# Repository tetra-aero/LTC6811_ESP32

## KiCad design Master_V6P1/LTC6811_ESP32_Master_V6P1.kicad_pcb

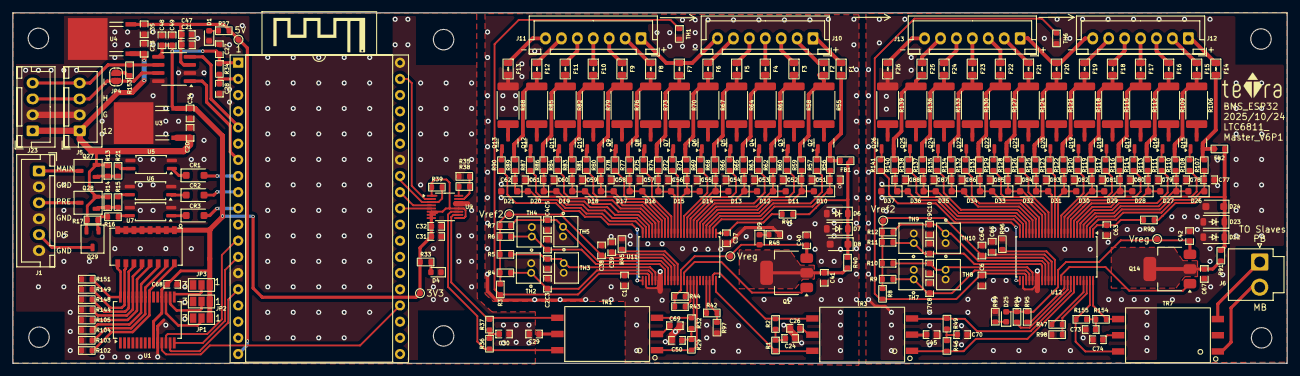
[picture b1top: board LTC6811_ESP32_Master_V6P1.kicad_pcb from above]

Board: 2 copper layers, 200.0 x 55.0 mm, 341 parts (1 on the bottom side), 253 nets.

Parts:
C1, C2, C3, C4, C5, C6, C7, C8, C9, C10, C27, C28, C32, C37, C41, C47, C49, C51, C52, C53, C54, C55, C56, C57, C58, C59, C60, C61, C62, C63, C67, C68, C77, C78, C79, C80, C81, C82, C83, C84, C85, C86, C87, C88: 100nF/100V; C_0603_1608Metric
C20, C33: 2.2uF/25V; C_0603_1608Metric
C21, C48: 1nF/16V; C_0603_1608Metric
C24, C26, C29, C30, C45, C50, C69, C70, C73, C74: 10nF/100V; C_0603_1608Metric
C31, C34, C35, C38, C39, C64, C65: 1uF/25V; C_0603_1608Metric
C40, C42: 4.7uF/16V; C_0603_1608Metric
CR1, CR2, CR3: S-562T; D_SOD-123F
D1, D4, D9, D25: LED Red; LED_0603_1608Metric
D6, D7, D22, D23: 1N4148W; D_SOD-123
D8, D24: BZT52H-C62; D_SOD-123F
D10, D11, D12, D13, D14, D15, D16, D17, D18, D19, D20, D21, D26, D27, D28, D29, D30, D31, D32, D33, D34, D35, D36, D37: PDZ7.5B; D_SOD-323_HandSoldering
F1, F2, F3, F4, F5, F6, F7, F8, F9, F10, F11, F12, F13, F14, F15, F16, F17, F18, F19, F20, F21, F22, F23, F24, F25, F26: MPZ2012S102ATD25; Fuse_0805_2012Metric
FB1, FB2: BLM18PG330SN1D; R_0603_1608Metric
J1: B6P-XH; JST_XH_B6B-XH-A_1x06_P2.50mm_Vertical
J3, J4, J7, J18, J19, J21: Hole /NC; MountingHole_3.2mm_M3_ISO7380
J5, J23: CAN; JST_XH_B4B-XH-A_1x04_P2.50mm_Vertical
J6: B2P-VH-B; JST_VH_B2P-VH-B_1x02_P3.96mm_Vertical
J10, J11, J12, J13: B7B-XH-A; JST_XH_B7B-XH-A_1x07_P2.50mm_Vertical_BAT_6S
JP1, JP2, JP3: SolderJumper_3_Bridged12; SolderJumper-3_P1.3mm_Open_Pad1.0x1.5mm_NumberLabels
JP4: SolderJumper_2_Open; SolderJumper-2_P1.3mm_Open_RoundedPad1.0x1.5mm
LOGO1, LOGO2: teTra /NC; teTra-LOGO
Q1, Q14: NSV1C201MZ4; SOT-223
Q2, Q3, Q4, Q5, Q6, Q7, Q8, Q9, Q10, Q11, Q12, Q13, Q15, Q16, Q17, Q18, Q19, Q20, Q21, Q22, Q23, Q24, Q25, Q26: TSM2323; SOT-23
Q27, Q28, Q29: SSM3J332R,LF; TSOT-23
R1, R2, R36, R37, R46, R49: 49.9R; R_0603_1608Metric
R3, R4, R5, R6, R7, R8, R9, R10, R11, R12, R13, R14, R16, R34, R102, R103, R104, R105, R144, R148, R149, R151: 10K; R_0603_1608Metric
R15, R17, R21, R35, R38, R42, R47, R97, R98: 1K; R_0603_1608Metric
R27, R33: 470R; R_0603_1608Metric
R29, R32, R154, R155: 51R; R_0603_1608Metric
R39: 2K; R_0603_1608Metric
R40, R41, R56, R59, R62, R65, R68, R71, R74, R77, R80, R83, R86, R89, R91, R92, R107, R110, R113, R116, R119, R122, R125, R128, R131, R134, R137, R140: 100R; R_0603_1608Metric
R43, R45, R94, R96: 0; R_0603_1608Metric
R44, R95: 1M; R_0603_1608Metric
R48, R99: 1.2K; R_0603_1608Metric
R55, R58, R61, R64, R67, R70, R73, R76, R79, R82, R85, R88, R106, R109, R112, R115, R118, R121, R124, R127, R130, R133, R136, R139: 36R 1W 2512; R_2512_6332Metric
R57, R60, R63, R66, R69, R72, R75, R78, R81, R84, R87, R90, R108, R111, R114, R117, R120, R123, R126, R129, R132, R135, R138, R141: 3.3K; R_0603_1608Metric
R153: 120R; R_0603_1608Metric
SW1: 218-8LPSTJ; SW_218-8LPSTJ_11.33×6.05_P1.27
TH1, TH6: 10K NTC SMD; R_0603_1608Metric
TH2, TH3, TH4, TH5, TH7, TH8, TH9, TH10: 10K NTC; JST_ZR_B2B-ZR_1x02_P1.50mm_Vertical
TP1: 5V; TestPoint_Pad_D1.0mm
TP2: 3V3; TestPoint_Pad_D1.0mm
TP3, TP5: Vreg; TestPoint_Pad_D1.0mm
TP4, TP6: Vref2; TestPoint_Pad_D1.0mm
TR1, TR3, TR7: HM2108NL
U1: MCP23017T-E/SS; SSOP-28_5.3x10.2mm_P0.65mm
U2: MCP2562T-E/SN; SOIC-8_3.9x4.9mm_P1.27mm
U3: BD33FC0FP-E2; TO252-3_ROM
U4: BD50FC0FP-E2; TO252-3_ROM
U5, U6, U7: TLP291; SOIC-4_4.55x2.6mm_P1.27mm
U8: ESP32-DevKitC V4; ESP32-DevKitc V4_DIP-38_27.9mm×48.2mm
U9: LTC6820; MSOP-16_3x4mm_P0.5mm
U11, U12: LTC6811HG-1; TSSOP-48_6.1x12.5mm_P0.5mm

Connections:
+3V3: C27.2, C31.2, C32.1, C34.2, C48.1, C49.1, C68.2, JP1.1 (A), JP2.1 (A), JP3.1 (A), R33.2, R34.1, R39.1, SW1.1, SW1.2, SW1.3, SW1.4, SW1.5, SW1.6, SW1.7, SW1.8, TP2.1, U1.9 (VDD), U1.18 (~RESET), U2.5 (Vio), U3.3 (Vo), U8.1 (3V3), U9.1 (EN), U9.6 (Vcc0), U9.7 (POL), U9.8 (PHA), U9.9 (VCC), U9.12 (MSTR)
+5V: C21.1, C35.2, C47.1, R27.2, TP1.1, U2.3 (VDD), U4.3 (Vo), U8.19 (5V)
+12V: C20.1, C33.1, J5.1, J23.1, Q27.2 (S), Q28.2 (S), Q29.2 (S), R13.2, R14.2, R16.2, U3.1 (Vcc), U4.1 (Vcc)
/CAN/CAN_H: J5.3, J23.3, JP4.1 (A), U2.7 (CANH)
/CAN/CAN_L: J5.4, J23.4, R153.1, U2.6 (CANL)
/CAN/RXD: U2.4 (RXD), U8.5 (IO34)
/CAN/TXD: U2.1 (TXD), U8.7 (IO32)
/MCU/Discharge_Relay: J1.5, Q29.3 (D)
/MCU/Discharge_Relay_Control: CR3.2, U8.10 (IO26)
/MCU/HSPI_CS: U1.11 (~CS), U8.23 (IO15)
/MCU/HSPI_MISO: U1.14 (SO), U8.13 (IO12)
/MCU/HSPI_MOSI: U1.13 (SI), U8.15 (IO13)
/MCU/HSPI_SCK: U1.12 (SCK), U8.12 (IO14)
/MCU/IM: R37.1, TR1.4, U9.10 (IM)
/MCU/IP: R36.2, TR1.6, U9.11 (IP)
/MCU/Main_Relay: J1.1, Q27.3 (D)
/MCU/Main_Relay_Control: CR1.2, U8.8 (IO33)
/MCU/NRST: C28.2, R34.2, U8.2 (EN)
/MCU/Precharge_Relay: J1.3, Q28.3 (D)
/MCU/Precharge_Relay_Control: CR2.2, U8.9 (IO25)
/MCU/VSPI_CS: U8.29 (IO5), U9.5 (CSB)
/MCU/VSPI_MISO: R39.2, U8.31 (IO19), U9.3 (MISO)
/MCU/VSPI_MOSI: U8.37 (IO23), U9.2 (MOSI)
/MCU/VSPI_SCK: U8.30 (IO18), U9.4 (SCK)
/Slaves/LTC6811_1/BAT+: D6.1 (K), D7.1 (K), D8.1 (K), FB1.1, R40.1, R41.1
/Slaves/LTC6811_1/C1: F12.1, J11.1 (Pin_2)
/Slaves/LTC6811_1/C1_G: F13.1, J11.0 (Pin_1)
/Slaves/LTC6811_1/C2: F11.1, J11.2 (Pin_3)
/Slaves/LTC6811_1/C3: F10.1, J11.3 (Pin_4)
/Slaves/LTC6811_1/C4: F9.1, J11.4 (Pin_5)
/Slaves/LTC6811_1/C5: F8.1, J11.5 (Pin_6)
/Slaves/LTC6811_1/C6: F7.1, J10.0 (Pin_1), J11.6 (Pin_7)
/Slaves/LTC6811_1/C7: F6.1, J10.1 (Pin_2)
/Slaves/LTC6811_1/C8: F5.1, J10.2 (Pin_3)
/Slaves/LTC6811_1/C9: F4.1, J10.3 (Pin_4)
/Slaves/LTC6811_1/C10: F3.1, J10.4 (Pin_5)
/Slaves/LTC6811_1/C11: F2.1, J10.5 (Pin_6)
/Slaves/LTC6811_1/C12: F1.1, J10.6 (Pin_7)
/Slaves/LTC6811_1/DRIVE: Q1.1 (B), U11.38 (DRIVE)
/Slaves/LTC6811_1/IMA: R32.1, TR1.3, U11.41 (IMA)
/Slaves/LTC6811_1/IMB: R2.1, TR3.4, U11.47 (IMB)
/Slaves/LTC6811_1/IPA: R29.2, TR1.1, U11.42 (IPA)
/Slaves/LTC6811_1/IPB: R1.2, TR3.6, U11.48 (IPB)
/Slaves/LTC6811_1/T1: C1.1, R3.2, TH1.1, U11.27 (GPIO1)
/Slaves/LTC6811_1/T2: C2.1, R4.1, TH2.1, U11.28 (GPIO2)
/Slaves/LTC6811_1/T3: C3.1, R5.1, TH3.1, U11.29 (GPIO3)
/Slaves/LTC6811_1/T4: C4.1, R6.1, TH4.1, U11.32 (GPIO4)
/Slaves/LTC6811_1/T5: C5.1, R7.1, TH5.1, U11.33 (GPIO5)
/Slaves/LTC6811_1/Vref2: C38.1, R3.1, R4.2, R5.2, R6.2, R7.2, TP4.1, U11.34 (Vref2)
/Slaves/LTC6811_1/Vreg: C40.1, D9.2 (A), Q1.3 (E), R43.2, R44.2, TP3.1, U11.37 (Vreg)
/Slaves/LTC6811_1/cell1/C: C62.1, D20.2 (A), D21.1 (K), R89.1, U11.24 (C1)
/Slaves/LTC6811_1/cell1/C+: F12.2, Q13.2 (S), R85.1, R89.2
/Slaves/LTC6811_1/cell1/S: R90.1, U11.25 (S1)
/Slaves/LTC6811_1/cell2/C: C61.1, D19.2 (A), D20.1 (K), R86.1, U11.22 (C2)
/Slaves/LTC6811_1/cell2/C+: F11.2, Q12.2 (S), R82.1, R86.2
/Slaves/LTC6811_1/cell2/S: R87.1, U11.23 (S2)
/Slaves/LTC6811_1/cell3/C: C60.1, D18.2 (A), D19.1 (K), R83.1, U11.20 (C3)
/Slaves/LTC6811_1/cell3/C+: F10.2, Q11.2 (S), R79.1, R83.2
/Slaves/LTC6811_1/cell3/S: R84.1, U11.21 (S3)
/Slaves/LTC6811_1/cell4/C: C59.1, D17.2 (A), D18.1 (K), R80.1, U11.18 (C4)
/Slaves/LTC6811_1/cell4/C+: F9.2, Q10.2 (S), R76.1, R80.2
/Slaves/LTC6811_1/cell4/S: R81.1, U11.19 (S4)
/Slaves/LTC6811_1/cell5/C: C58.1, D16.2 (A), D17.1 (K), R77.1, U11.16 (C5)
/Slaves/LTC6811_1/cell5/C+: F8.2, Q9.2 (S), R73.1, R77.2
/Slaves/LTC6811_1/cell5/S: R78.1, U11.17 (S5)
/Slaves/LTC6811_1/cell6/C: C57.1, D15.2 (A), D16.1 (K), R74.1, U11.14 (C6)
/Slaves/LTC6811_1/cell6/C+: F7.2, Q8.2 (S), R70.1, R74.2
/Slaves/LTC6811_1/cell6/S: R75.1, U11.15 (S6)
/Slaves/LTC6811_1/cell7/C: C56.1, D14.2 (A), D15.1 (K), R71.1, U11.12 (C7)
/Slaves/LTC6811_1/cell7/C+: F6.2, Q7.2 (S), R67.1, R71.2
/Slaves/LTC6811_1/cell7/S: R72.1, U11.13 (S7)
/Slaves/LTC6811_1/cell8/C: C55.1, D13.2 (A), D14.1 (K), R68.1, U11.10 (C8)
/Slaves/LTC6811_1/cell8/C+: F5.2, Q6.2 (S), R64.1, R68.2
/Slaves/LTC6811_1/cell8/S: R69.1, U11.11 (S8)
/Slaves/LTC6811_1/cell9/S: R66.1, U11.9 (S9)
/Slaves/LTC6811_1/cell10/C: C53.1, D11.2 (A), D12.1 (K), R62.1, U11.6 (C10)
/Slaves/LTC6811_1/cell10/C+: F3.2, Q4.2 (S), R58.1, R62.2
/Slaves/LTC6811_1/cell10/C-: F4.2, Q5.2 (S), R61.1, R65.2
/Slaves/LTC6811_1/cell10/CM: C54.1, D12.2 (A), D13.1 (K), R65.1, U11.8 (C9)
/Slaves/LTC6811_1/cell10/S: R63.1, U11.7 (S10)
/Slaves/LTC6811_1/cell11/C: C52.1, D10.2 (A), D11.1 (K), R59.1, U11.4 (C11)
/Slaves/LTC6811_1/cell11/C+: F2.2, Q3.2 (S), R55.1, R59.2
/Slaves/LTC6811_1/cell11/S: R60.1, U11.5 (S11)
/Slaves/LTC6811_1/cell12/C: C51.1, D10.1 (K), R56.1, U11.2 (C12)
/Slaves/LTC6811_1/cell12/C+: F1.2, FB1.2, Q2.2 (S), R56.2
/Slaves/LTC6811_1/cell12/S: R57.1, U11.3 (S12)
/Slaves/LTC6811_2/BAT+: D22.1 (K), D23.1 (K), D24.1 (K), FB2.1, R91.1, R92.1
/Slaves/LTC6811_2/C1: F25.1, J13.1 (Pin_2)
/Slaves/LTC6811_2/C1_G: F26.1, J13.0 (Pin_1)
/Slaves/LTC6811_2/C2: F24.1, J13.2 (Pin_3)
/Slaves/LTC6811_2/C3: F23.1, J13.3 (Pin_4)
/Slaves/LTC6811_2/C4: F22.1, J13.4 (Pin_5)
/Slaves/LTC6811_2/C5: F21.1, J13.5 (Pin_6)
/Slaves/LTC6811_2/C6: F20.1, J12.0 (Pin_1), J13.6 (Pin_7)
/Slaves/LTC6811_2/C7: F19.1, J12.1 (Pin_2)
/Slaves/LTC6811_2/C8: F18.1, J12.2 (Pin_3)
/Slaves/LTC6811_2/C9: F17.1, J12.3 (Pin_4)
/Slaves/LTC6811_2/C10: F16.1, J12.4 (Pin_5)
/Slaves/LTC6811_2/C11: F15.1, J12.5 (Pin_6)
/Slaves/LTC6811_2/C12: F14.1, J12.6 (Pin_7)
/Slaves/LTC6811_2/DRIVE: Q14.1 (B), U12.38 (DRIVE)
/Slaves/LTC6811_2/IMA: R49.1, TR3.3, U12.41 (IMA)
/Slaves/LTC6811_2/IMB: R155.1, TR7.6, U12.47 (IMB)
/Slaves/LTC6811_2/IPA: R46.2, TR3.1, U12.42 (IPA)
/Slaves/LTC6811_2/IPB: R154.2, TR7.4, U12.48 (IPB)
/Slaves/LTC6811_2/T1: C6.1, R8.2, TH6.1, U12.27 (GPIO1)
/Slaves/LTC6811_2/T2: C7.1, R9.1, TH7.1, U12.28 (GPIO2)
/Slaves/LTC6811_2/T3: C8.1, R10.1, TH8.1, U12.29 (GPIO3)
/Slaves/LTC6811_2/T4: C9.1, R11.1, TH9.1, U12.32 (GPIO4)
/Slaves/LTC6811_2/T5: C10.1, R12.1, TH10.1, U12.33 (GPIO5)
/Slaves/LTC6811_2/Vref2: C64.1, R8.1, R9.2, R10.2, R11.2, R12.2, TP6.1, U12.34 (Vref2)
/Slaves/LTC6811_2/Vreg: C42.1, D25.2 (A), Q14.3 (E), R94.2, R95.2, TP5.1, U12.37 (Vreg)
/Slaves/LTC6811_2/cell1/C: C88.1, D36.2 (A), D37.1 (K), R140.1, U12.24 (C1)
/Slaves/LTC6811_2/cell1/C+: F25.2, Q26.2 (S), R136.1, R140.2
/Slaves/LTC6811_2/cell1/S: R141.1, U12.25 (S1)
/Slaves/LTC6811_2/cell2/C: C87.1, D35.2 (A), D36.1 (K), R137.1, U12.22 (C2)
/Slaves/LTC6811_2/cell2/C+: F24.2, Q25.2 (S), R133.1, R137.2
/Slaves/LTC6811_2/cell2/S: R138.1, U12.23 (S2)
/Slaves/LTC6811_2/cell3/C: C86.1, D34.2 (A), D35.1 (K), R134.1, U12.20 (C3)
/Slaves/LTC6811_2/cell3/C+: F23.2, Q24.2 (S), R130.1, R134.2
/Slaves/LTC6811_2/cell3/S: R135.1, U12.21 (S3)
/Slaves/LTC6811_2/cell4/C: C85.1, D33.2 (A), D34.1 (K), R131.1, U12.18 (C4)
/Slaves/LTC6811_2/cell4/C+: F22.2, Q23.2 (S), R127.1, R131.2
/Slaves/LTC6811_2/cell4/S: R132.1, U12.19 (S4)
/Slaves/LTC6811_2/cell5/C: C84.1, D32.2 (A), D33.1 (K), R128.1, U12.16 (C5)
/Slaves/LTC6811_2/cell5/C+: F21.2, Q22.2 (S), R124.1, R128.2
/Slaves/LTC6811_2/cell5/S: R129.1, U12.17 (S5)
/Slaves/LTC6811_2/cell6/C: C83.1, D31.2 (A), D32.1 (K), R125.1, U12.14 (C6)
/Slaves/LTC6811_2/cell6/C+: F20.2, Q21.2 (S), R121.1, R125.2
/Slaves/LTC6811_2/cell6/S: R126.1, U12.15 (S6)
/Slaves/LTC6811_2/cell7/C: C82.1, D30.2 (A), D31.1 (K), R122.1, U12.12 (C7)
/Slaves/LTC6811_2/cell7/C+: F19.2, Q20.2 (S), R118.1, R122.2
/Slaves/LTC6811_2/cell7/S: R123.1, U12.13 (S7)
/Slaves/LTC6811_2/cell8/C: C81.1, D29.2 (A), D30.1 (K), R119.1, U12.10 (C8)
/Slaves/LTC6811_2/cell8/C+: F18.2, Q19.2 (S), R115.1, R119.2
/Slaves/LTC6811_2/cell8/S: R120.1, U12.11 (S8)
/Slaves/LTC6811_2/cell9/S: R117.1, U12.9 (S9)
/Slaves/LTC6811_2/cell10/C: C79.1, D27.2 (A), D28.1 (K), R113.1, U12.6 (C10)
/Slaves/LTC6811_2/cell10/C+: F16.2, Q17.2 (S), R109.1, R113.2
/Slaves/LTC6811_2/cell10/C-: F17.2, Q18.2 (S), R112.1, R116.2
/Slaves/LTC6811_2/cell10/CM: C80.1, D28.2 (A), D29.1 (K), R116.1, U12.8 (C9)
/Slaves/LTC6811_2/cell10/S: R114.1, U12.7 (S10)
/Slaves/LTC6811_2/cell11/C: C78.1, D26.2 (A), D27.1 (K), R110.1, U12.4 (C11)
/Slaves/LTC6811_2/cell11/C+: F15.2, Q16.2 (S), R106.1, R110.2
/Slaves/LTC6811_2/cell11/S: R111.1, U12.5 (S11)
/Slaves/LTC6811_2/cell12/C: C77.1, D26.1 (K), R107.1, U12.2 (C12)
/Slaves/LTC6811_2/cell12/C+: F14.2, FB2.2, Q15.2 (S), R107.2
/Slaves/LTC6811_2/cell12/S: R108.1, U12.3 (S12)
/Slaves/MB: J6.2, TR7.1
/Slaves/PB: J6.1, TR7.3
GND: C20.2, C21.2, C27.1, C28.1, C29.1, C30.1, C31.1, C32.2, C33.2, C34.1, C35.1, C47.2, C48.2, C49.2, C68.1, D1.1 (K), D4.1 (K), J1.2, J1.4, J1.6, J5.2, J23.2, JP1.3 (B), JP2.3 (B), JP3.3 (B), R35.1, R102.1, R103.1, R104.1, R105.1, R144.1, R148.1, R149.1, R151.1, U1.10 (VSS), U2.2 (VSS), U2.8 (STBY), U3.2 (GND), U4.2 (GND), U5.2, U5.3, U6.2, U6.3, U7.2, U7.3, U8.14 (GND), U8.32 (GND), U8.38 (GND), U9.13 (SLOW), U9.14 (GND)
GND_PACK: C1.2, C2.2, C3.2, C4.2, C5.2, C6.2, C7.2, C8.2, C9.2, C10.2, C24.2, C26.2, C37.2, C38.2, C39.2, C40.2, C41.2, C42.2, C45.2, C50.2, C51.2, C52.2, C53.2, C54.2, C55.2, C56.2, C57.2, C58.2, C59.2, C60.2, C61.2, C62.2, C63.2, C64.2, C65.2, C67.2, C69.2, C70.2, C73.1, C74.2, C77.2, C78.2, C79.2, C80.2, C81.2, C82.2, C83.2, C84.2, C85.2, C86.2, C87.2, C88.2, D6.2 (A), D7.2 (A), D8.2 (A), D21.2 (A), D22.2 (A), D23.2 (A), D24.2 (A), D37.2 (A), F13.2, F26.2, R45.2, R48.2, R88.1, R96.2, R97.2, R98.2, R99.2, R139.1, TH1.2, TH2.2, TH3.2, TH4.2, TH5.2, TH6.2, TH7.2, TH8.2, TH9.2, TH10.2, U11.26 (C0), U11.30 (V-**), U11.31 (V-), U12.26 (C0), U12.30 (V-**), U12.31 (V-)
unnamed: C24.1, R1.1, R2.2
unnamed: C26.1, TR3.5
unnamed: C29.2, TR1.5
unnamed: C30.2, R36.1, R37.2
unnamed: C41.1, Q1.2 (C), Q1.4 (C), R40.2
unnamed: C45.1, TR3.2
unnamed: C50.1, R29.1, R32.2
unnamed: C67.1, Q14.2 (C), Q14.4 (C), R91.2
unnamed: C69.1, TR1.2
unnamed: C70.1, R46.1, R49.2
unnamed: C73.2, R154.1, R155.2
unnamed: C74.1, TR7.5
unnamed: CR1.1, U5.1
unnamed: CR2.1, U6.1
unnamed: CR3.1, U7.1
unnamed: D1.2 (A), R27.1
unnamed: D4.2 (A), R33.1
unnamed: D9.1 (K), R48.1
unnamed: D25.1 (K), R99.1
unnamed: JP1.2 (C), U1.17 (A2)
unnamed: JP2.2 (C), U1.16 (A1)
unnamed: JP3.2 (C), U1.15 (A0)
unnamed: JP4.2 (B), R153.2
unnamed: Q2.3 (D), R55.2
unnamed: Q2.1 (G), R57.2
unnamed: Q3.3 (D), R58.2
unnamed: Q3.1 (G), R60.2
unnamed: Q4.3 (D), R61.2
unnamed: Q4.1 (G), R63.2
unnamed: Q5.3 (D), R64.2
unnamed: Q5.1 (G), R66.2
unnamed: Q6.3 (D), R67.2
unnamed: Q6.1 (G), R69.2
unnamed: Q7.3 (D), R70.2
unnamed: Q7.1 (G), R72.2
unnamed: Q8.3 (D), R73.2
unnamed: Q8.1 (G), R75.2
unnamed: Q9.3 (D), R76.2
unnamed: Q9.1 (G), R78.2
unnamed: Q10.3 (D), R79.2
unnamed: Q10.1 (G), R81.2
unnamed: Q11.3 (D), R82.2
unnamed: Q11.1 (G), R84.2
unnamed: Q12.3 (D), R85.2
unnamed: Q12.1 (G), R87.2
unnamed: Q13.3 (D), R88.2
unnamed: Q13.1 (G), R90.2
unnamed: Q15.3 (D), R106.2
unnamed: Q15.1 (G), R108.2
unnamed: Q16.3 (D), R109.2
unnamed: Q16.1 (G), R111.2
unnamed: Q17.3 (D), R112.2
unnamed: Q17.1 (G), R114.2
unnamed: Q18.3 (D), R115.2
unnamed: Q18.1 (G), R117.2
unnamed: Q19.3 (D), R118.2
unnamed: Q19.1 (G), R120.2
unnamed: Q20.3 (D), R121.2
unnamed: Q20.1 (G), R123.2
unnamed: Q21.3 (D), R124.2
unnamed: Q21.1 (G), R126.2
unnamed: Q22.3 (D), R127.2
unnamed: Q22.1 (G), R129.2
unnamed: Q23.3 (D), R130.2
unnamed: Q23.1 (G), R132.2
unnamed: Q24.3 (D), R133.2
unnamed: Q24.1 (G), R135.2
unnamed: Q25.3 (D), R136.2
unnamed: Q25.1 (G), R138.2
unnamed: Q26.3 (D), R139.2
unnamed: Q26.1 (G), R141.2
unnamed: Q27.1 (G), R13.1, R21.2
unnamed: Q28.1 (G), R14.1, R15.2
unnamed: Q29.1 (G), R16.1, R17.2
unnamed: R15.1, U6.4
unnamed: R17.1, U7.4
unnamed: R21.1, U5.4
unnamed: R102.2, SW1.16, U1.21 (GPA0)
unnamed: R103.2, SW1.15, U1.22 (GPA1)
unnamed: R104.2, SW1.14, U1.23 (GPA2)
unnamed: R105.2, SW1.13, U1.24 (GPA3)
unnamed: R144.2, SW1.12, U1.25 (GPA4)
unnamed: R148.2, SW1.11, U1.26 (GPA5)
unnamed: R149.2, SW1.10, U1.27 (GPA6)
unnamed: R151.2, SW1.9, U1.28 (GPA7)
unnamed: R38.2, U9.16 (IBIAS)
unnamed: R35.2, R38.1, U9.15 (ICMP)
unnamed: R45.1, U11.36 (DTEN)
unnamed: R42.1, U11.45 (IBIAS)
unnamed: R42.2, R97.1, U11.46 (ICMP)
unnamed: R43.1, U11.40 (ISOMD)
unnamed: C37.1, R41.2, U11.1 (V+)
unnamed: C39.1, U11.35 (Vref1)
unnamed: R44.1, U11.39 (WDT)
unnamed: R96.1, U12.36 (DTEN)
unnamed: R47.1, U12.45 (IBIAS)
unnamed: R47.2, R98.1, U12.46 (ICMP)
unnamed: R94.1, U12.40 (ISOMD)
unnamed: C63.1, R92.2, U12.1 (V+)
unnamed: C65.1, U12.35 (Vref1)
unnamed: R95.1, U12.39 (WDT)

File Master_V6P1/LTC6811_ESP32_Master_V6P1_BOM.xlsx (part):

Item | Qty | Reference | Value | Description | Datasheet | Footprint | Link | MPN | weight | total weight
1 | 44 | C1,C2,C3,C4,C5,C6,C7,C8,C9,C10,C27,C28,C32,C37,C41,C47,C49,C51,C52,C53,C54,C55,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 | 100nF/100V | 0.1 uF ±10% 100V Ceramic Capacitor X7R 0603 (1608 Metric) | https://www.digikey.jp/en/products/detail/samsung-electro-me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 | Capacitor_SMD:C_0603_1608Metric | https://www.digikey.jp/en/products/detail/samsung-electro-me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 | CL10B104KC8NNNC | 0.0063 | 0.2772
2 | 2 | C20,C33 | 2.2uF/25V | 2.2 uF ±10% 25V Ceramic Capacitor X5R 0603 (1608 Metric) | https://search.murata.co.jp/Ceramy/image/img/A01X/G101/ENG/G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 | Capacitor_SMD:C_0603_1608Metric | https://www.digikey.jp/en/products/detail/murata-electronics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 | GRM188R61E225KA12D | 0.0063 | 0.0126
3 | 2 | C21,C48 | 1nF/16V | 1000 pF ±10% 16V Ceramic Capacitor X7R 0603 (1608 Metric) | https://connect.kemet.com:7667/gateway/IntelliData-Component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 | Capacitor_SMD:C_0603_1608Metric | https://www.digikey.jp/en/products/detail/kemet/C0603C102K4R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 | C0603C102K4RECAUTO | 0.0063 | 0.0126
4 | 10 | C24,C26,C29,C30,C45,C50,C69,C70,C73,C74 | 10nF/100V | 10000 pF ±10% 100V Ceramic Capacitor X7R 0603 (1608 Metric) | https://content.kemet.com/datasheets/KEM_X7R_FT_VW_AUDI.pdf | Capacitor_SMD:C_0603_1608Metric | https://www.digikey.jp/en/products/detail/kemet/C0603X103K1R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 | C0603X103K1RAC3316 | 0.0063 | 0.063
5 | 7 | C31,C34,C35,C38,C39,C64,C65 | 1uF/25V | 1 uF ±10% 25V Ceramic Capacitor X7R 0603 (1608 Metric) | https://mm.digikey.com/Volume0/opasdata/d220001/medias/docus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 | Capacitor_SMD:C_0603_1608Metric | https://www.digikey.jp/en/products/detail/samsung-electro-me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 | CL10B105KA8NNNC | 0.0063 | 0.0441
6 | 2 | C40,C42 | 4.7uF/16V | 4.7 uF ±10% 16V Ceramic Capacitor X5R 0603 (1608 Metric) | https://mm.digikey.com/Volume0/opasdata/d220001/medias/docus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 | Capacitor_SMD:C_0603_1608Metric | https://www.digikey.jp/en/products/detail/samsung-electro-me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 | CL10A475KO8NNNC | 0.0063 | 0.0126
7 | 3 | CR1,CR2,CR3 | S-562T | CURRENT REGULATOR DIODES 100V 5. | https://www.semitec-global.com/uploads/2022/01/P22-23-CRD.pdf | Diode_SMD:D_SOD-123F | https://www.digikey.jp/en/products/detail/semitec-usa-corp/S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 | S-562T
8 | 4 | D1,D4,D9,D25 | LED Red | Red 631nm LED Indication - Discrete 2V 0603 (1608 Metric) | https://optoelectronics.liteon.com/upload/download/DS-22-99-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 | LED_SMD:LED_0603_1608Metric | https://www.digikey.jp/en/products/detail/liteon/LTST-C190KR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 | LTST-C190KRKT | 0.028 | 0.112
9 | 4 | D6,D7,D22,D23 | 1N4148W | Diode 100 V 300mA Surface Mount SOD-123 | https://www.diodes.com/assets/Datasheets/BAV16W_1N4148W.pdf | Diode_SMD:D_SOD-123 | https://www.digikey.jp/en/products/detail/diodes-incorporate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 | 1N4148W-7-F | 0.01 | 0.04
10 | 2 | D8,D24 | BZT52H-C62 | Zener Diode 62 V 375 mW ±5% Surface Mount SOD-123F | https://assets.nexperia.com/documents/data-sheet/BZT52H_SER.pdf | Diode_SMD:D_SOD-123F | https://www.digikey.jp/en/products/detail/nexperia-usa-inc/B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 | BZT52H-C62,115 | 0.0098 | 0.0196
11 | 24 | D10,D11,D12,D13,D14,D15,D16,D17,D18,D19,D20,D21,D26,D27,D28,D29,D30,D31,D32,D33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 | PDZ7.5B | Zener Diode 7.6 V 400 mW ±2% Surface Mount SOD-323 | https://assets.nexperia.com/documents/data-sheet/PDZ-B_SER.pdf | Diode_SMD:D_SOD-323_HandSoldering | https://www.digikey.jp/en/products/detail/nexperia-usa-inc/P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 | PDZ7.5BZ | 0.001 | 0.024
12 | 26 | F1,F2,F3,F4,F5,F6,F7,F8,F9,F10,F11,F12,F13,F14,F15,F16,F17,F18,F19,F20,F21,F22,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 | MPZ2012S102ATD25 | 1 kOhms @ 100 MHz 1 Power Line Ferrite Bead 0805 (2012 Metric) 1.5A 150mOhm | https://product.tdk.com/en/system/files?file=dam/doc/product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 | Fuse:Fuse_0805_2012Metric | https://www.digikey.jp/en/products/detail/tdk-corporation/MP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 | MPZ2012S102ATD25 | 0.008 | 0.208
13 | 2 | FB1,FB2 | BLM18PG330SN1D | 33 Ohms @ 100 MHz 1 Power Line Ferrite Bead 0603 (1608 Metric) 3A 25mOhm | https://www.murata.com/en-us/products/productdata/8796738650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 | Resistor_SMD:R_0603_1608Metric | https://www.digikey.jp/en/products/detail/murata-electronics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 | BLM18PG330SN1D | 0.035 | 0.07
14 |  | J1 | B6B-XH-A | Connector Header Through Hole 6 position 0.098" (2.50mm) | https://www.jst-mfg.com/product/pdf/eng/eXH.pdf | Connector_JST:JST_XH_B6B-XH-A_1x06_P2.50mm_Vertical | https://www.digikey.jp/en/products/detail/jst-sales-america-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 | B6B-XH-A
15 | 2 | J5,J23 | CAN | Connector Header Through Hole 4 position 0.098" (2.50mm) | chrome-extension://efaidnbmnnnibpcajpcglclefindmkaj/https://www.jst-mfg.com/pro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 | Connector_JST:JST_XH_B4B-XH-A_1x04_P2.50mm_Vertical | https://www.digikey.jp/en/products/detail/jst-sales-america-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 | B4B-XH-A | 0.4 | 0.8
16 | 1 | J6 | B2P-VH-B | Connector Header Through Hole 2 position 0.100" (2.54mm) | https://tools.molex.com/pdm_docs/sd/705430001_sd.pdf | Connector_JST:JST_VH_B2P-VH-B_1x02_P3.96mm_Vertical | https://www.digikey.jp/en/products/detail/jst-sales-america-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 | B2P-VH | 0.58 | 0.58
17 | 4 | J10,J11,J12,J13 | B7B-XH-A | Connector Header Through Hole 7 position 0.098" (2.50mm) | https://www.jst-mfg.com/product/pdf/eng/eXH.pdf | Connector_JST:JST_XH_B7B-XH-A_1x07_P2.50mm_Vertical_BAT_6S | https://www.digikey.jp/en/products/detail/jst-sales-america-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 | B7B-XH-A | 0.652 | 2.608
18 | 2 | Q1,Q14 | NSV1C201MZ4 | Bipolar (BJT) Transistor NPN 100 V 2 A 100MHz 800 mW Surface Mount SOT-223 (TO-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 | https://www.onsemi.com/pdf/datasheet/nss1c201mz4-d.pdf | Package_TO_SOT_SMD:SOT-223 | https://www.digikey.jp/en/products/detail/onsemi/NSV1C201MZ4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 | NSV1C201MZ4T1G | 0.112 | 0.224
19 | 24 | Q2,Q3,Q4,Q5,Q6,Q7,Q8,Q9,Q10,Q11,Q12,Q13,Q15,Q16,Q17,Q18,Q19,Q20,Q21,Q22,Q23,Q24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 | TSM2323 | P-Channel 20 V 4.7A (Ta) 1.25W (Ta) Surface Mount SOT-23 | https://www.taiwansemi.com/assets/uploads/datasheet/TSM2323_F15.pdf | Package_TO_SOT_SMD:SOT-23 | https://www.digikey.jp/en/products/detail/taiwan-semiconduct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 | TSM2323CX RFG | 0.008 | 0.192
20 | 3 | Q27,Q28,Q28 | SSM3J332R,LF | P-MOSFET transistor, gate/source/drain | https://toshiba.semicon-storage.com/info/SSM3J332R_datasheet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 | PCM_Package_TO_SOT_SMD_AKL:TSOT-23 | https://www.digikey.jp/en/products/detail/toshiba-semiconduc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 | SSM3J332R,LF
21 | 6 | R1,R2,R36,R37,R46,R49 | 49.9R | 49.9 Ohms ±1% 0.1W, 1/10W Chip Resistor 0603 (1608 Metric) Automotive AEC-Q200 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 | https://industrial.panasonic.com/cdbs/www-data/pdf/RDA0000/A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 | Resistor_SMD:R_0603_1608Metric | https://www.digikey.jp/en/products/detail/panasonic-electron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 | ERJ-3EKF49R9V | 0.002 | 0.012
22 | 21 | R3,R4,R5,R6,R7,R8,R9,R10,R11,R12R13,R14,R16,,R34,R102,R103,R104,R105,R144,R148,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 | 10K | 10 kOhms ±1% 0.1W, 1/10W Chip Resistor 0603 (1608 Metric) Moisture Resistant Th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 | https://www.yageo.com/upload/media/product/products/datashee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 | Resistor_SMD:R_0603_1608Metric | https://www.digikey.jp/en/products/detail/yageo/RC0603FR-071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 | RC0603FR-0710KL | 0.002 | 0.042
23 | 2 | R27,R33 | 470R | 470 Ohms ±5% 0.1W, 1/10W Chip Resistor 0603 (1608 Metric) Moisture Resistant Th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 | https://www.yageo.com/upload/media/product/products/datashee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 | Resistor_SMD:R_0603_1608Metric | https://www.digikey.jp/en/products/detail/yageo/RC0603JR-074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 | RC0603JR-07470RL | 0.002 | 0.004
24 | 4 | R29,R32,R154,R155 | 51R | 51 Ohms ±5% 0.1W, 1/10W Chip Resistor 0603 (1608 Metric) Moisture Resistant Thi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 | https://www.yageo.com/upload/media/product/productsearch/dat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 | Resistor_SMD:R_0603_1608Metric | https://www.digikey.jp/en/products/detail/yageo/RC0603JR-075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 | RC0603JR-0751RL | 0.002 | 0.008
25 | 9 | R15,R17,R21,R35,R38,R42,R47,R97,R98 | 1K | 1 kOhms ±1% 0.1W, 1/10W Chip Resistor 0603 (1608 Metric) Moisture Resistant Thi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 | https://www.yageo.com/upload/media/product/products/datashee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 | Resistor_SMD:R_0603_1608Metric | https://www.digikey.jp/en/products/detail/yageo/RC0603FR-071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 | RC0603FR-071KL | 0.002 | 0.018
26 | 1 | R39 | 2K | 2 kOhms ±1% 0.1W, 1/10W Chip Resistor 0603 (1608 Metric) Moisture Resistant Thi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 | https://www.yageo.com/upload/media/product/app/datasheet/rch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 | Resistor_SMD:R_0603_1608Metric | https://www.digikey.jp/en/products/detail/yageo/RC0603FR-072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 | RC0603FR-072KL | 0.002 | 0.002
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
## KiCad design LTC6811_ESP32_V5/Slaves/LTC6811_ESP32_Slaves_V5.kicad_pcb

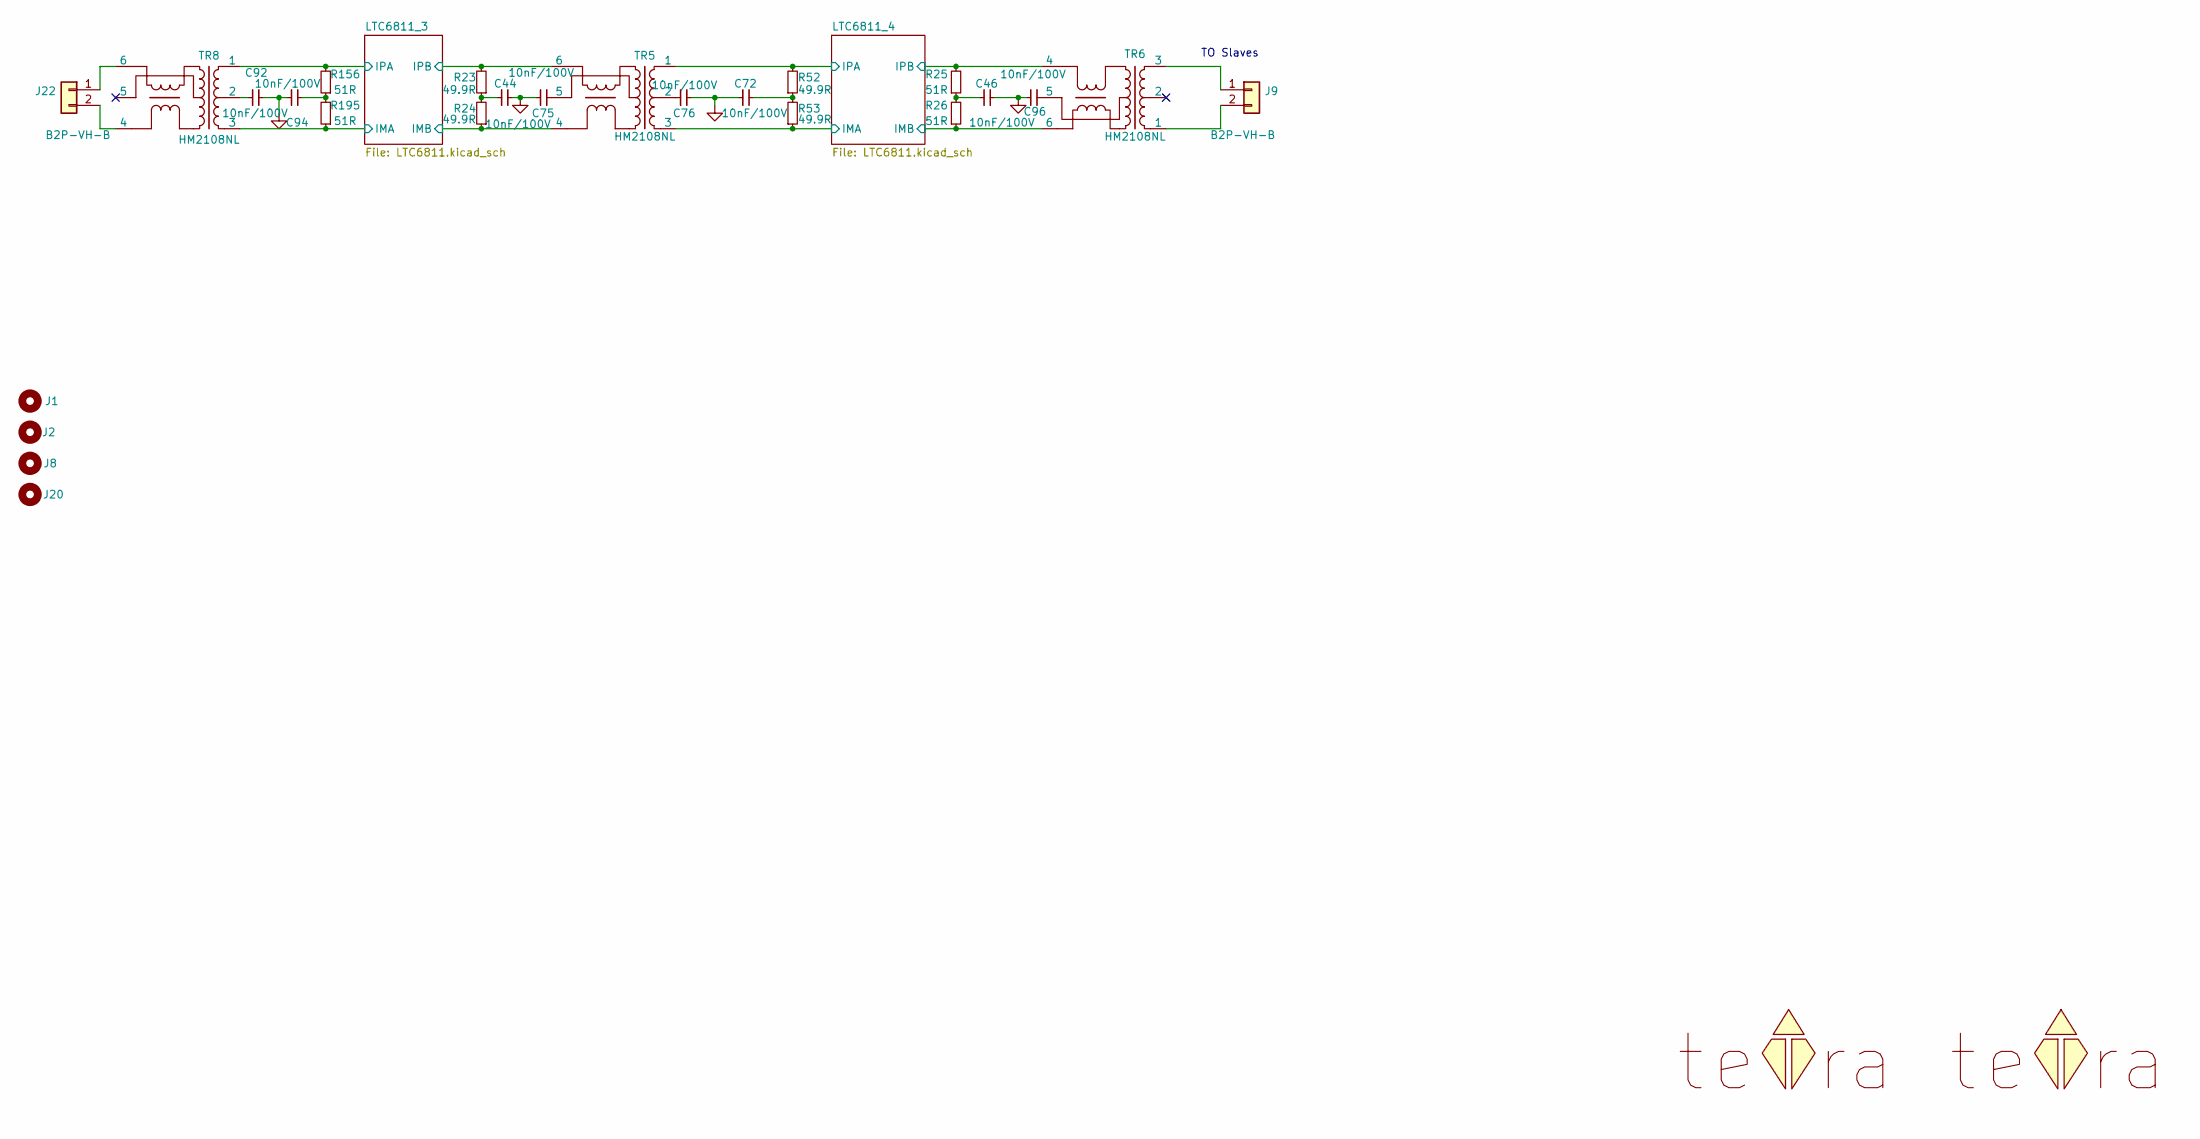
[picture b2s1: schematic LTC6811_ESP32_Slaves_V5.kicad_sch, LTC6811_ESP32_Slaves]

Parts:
C44, C46, C72, C75, C76, C92, C94, C96: 10nF/100V; C_0603_1608Metric; MPN C0603X103K1RAC3316
J1, J2, J8, J20: Hole /NC; MountingHole_3.2mm_M3_ISO7380; MPN N/A
J9, J22: B2P-VH-B; JST_VH_B2P-VH-B_1x02_P3.96mm_Vertical; MPN B2P-VH
LOGO1, LOGO2: teTra /NC; teTra-LOGO
R23, R24, R52, R53: 49.9R; R_0603_1608Metric; MPN ERJ-3EKF49R9V
R25, R26, R156, R195: 51R; R_0603_1608Metric; MPN RC0603JR-0751RL
TR5, TR6, TR8: HM2108NL; MPN HM2108NL

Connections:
/LTC6811_3/IMA: R195.1, TR8.3; also elsewhere on the board
/LTC6811_3/IMB: R24.1, TR5.4; also elsewhere on the board
/LTC6811_3/IPA: R156.2, TR8.1; also elsewhere on the board
/LTC6811_3/IPB: R23.2, TR5.6; also elsewhere on the board
/LTC6811_4/IMA: R53.1, TR5.3; also elsewhere on the board
/LTC6811_4/IMB: R26.1, TR6.6; also elsewhere on the board
/LTC6811_4/IPA: R52.2, TR5.1; also elsewhere on the board
/LTC6811_4/IPB: R25.2, TR6.4; also elsewhere on the board
GND_PACK: C44.2, C46.1, C72.2, C75.2, C76.2, C92.2, C94.2, C96.2; also elsewhere on the board
unnamed: C44.1, R23.1, R24.2
unnamed: C46.2, R25.1, R26.2
unnamed: C72.1, R52.1, R53.2
unnamed: C75.1, TR5.5
unnamed: C76.1, TR5.2
unnamed: C92.1, TR8.2
unnamed: C94.1, R156.1, R195.2
unnamed: C96.1, TR6.5
unnamed: J9.1, TR6.3
unnamed: J9.2, TR6.1
unnamed: J22.1, TR8.6
unnamed: J22.2, TR8.4

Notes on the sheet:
TO Slaves
